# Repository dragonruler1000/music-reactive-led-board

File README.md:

# music-reactive-led-board
a control board for macking powering and controling leds to be music/sound reactive

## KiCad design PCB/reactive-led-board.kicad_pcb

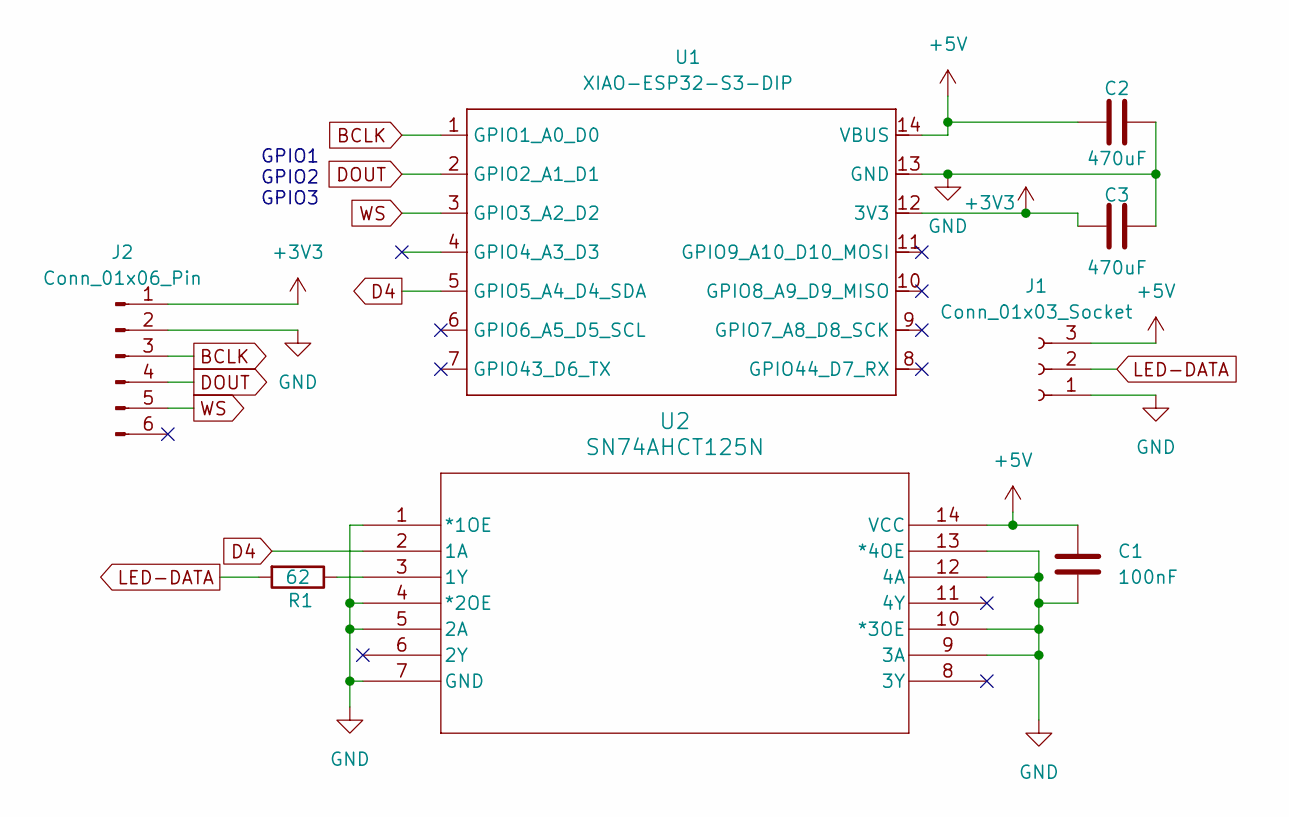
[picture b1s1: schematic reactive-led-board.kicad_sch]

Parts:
C1: 100nF; C_Rect_L7.2mm_W2.5mm_P5.00mm
C2, C3: 470uF; CP_Radial_D8.0mm_P3.50mm
J1: Conn_01x03_Socket; 691137710003
J2: Conn_01x06_Pin; PinHeader_1x06_P2.54mm_Vertical
R1: 62; R_Axial_DIN0204_L3.6mm_D1.6mm_P1.90mm_Vertical
U1: XIAO-ESP32-S3-DIP
U2: SN74AHCT125N; N14

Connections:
+3V3: C3.1, J2.1, U1.12 (3V3)
+5V: C1.1, C2.1, J1.3, U1.14 (VBUS), U2.14 (VCC)
BCLK: J2.3, U1.1 (GPIO1_A0_D0)
D4: U1.5 (GPIO5_A4_D4_SDA), U2.2 (1A)
DOUT: J2.4, U1.2 (GPIO2_A1_D1)
GND: C1.2, C2.2, C3.2, J1.1, J2.2, U1.13 (GND), U2.1 (*1OE), U2.4 (*2OE), U2.5 (2A), U2.7 (GND), U2.9 (3A), U2.10 (*3OE), U2.12 (4A), U2.13 (*4OE)
LED-DATA: J1.2, R1.2
unnamed: R1.1, U2.3 (1Y)
WS: J2.5, U1.3 (GPIO3_A2_D2)

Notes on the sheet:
GPIO1 GPIO2 GPIO3

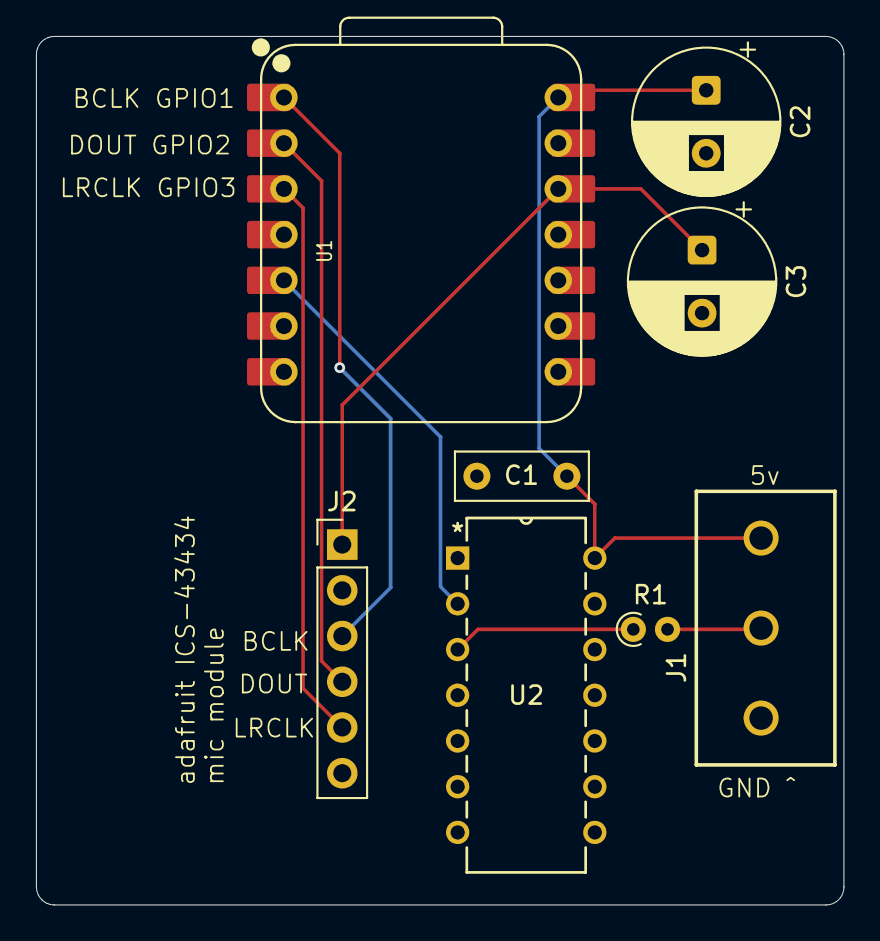
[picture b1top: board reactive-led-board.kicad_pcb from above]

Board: 2 copper layers, 44.9 x 48.3 mm, 8 parts (0 on the bottom side), 9 nets.

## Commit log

2026-06-22 started work on the led control board. it should now be done at least on the main control side of stuff.
2026-06-26 routed the treaces and selected the parts i am going to use.
2026-06-28 added 3d model for the xiao and added the connector for the mic module
2026-06-29 did some hard ware changes and update bom swaped to using a screw terminal and updated the links in the bom to match with the leds i am going to use
2026-06-29 update pcb page size
2026-06-29 saved the bom
